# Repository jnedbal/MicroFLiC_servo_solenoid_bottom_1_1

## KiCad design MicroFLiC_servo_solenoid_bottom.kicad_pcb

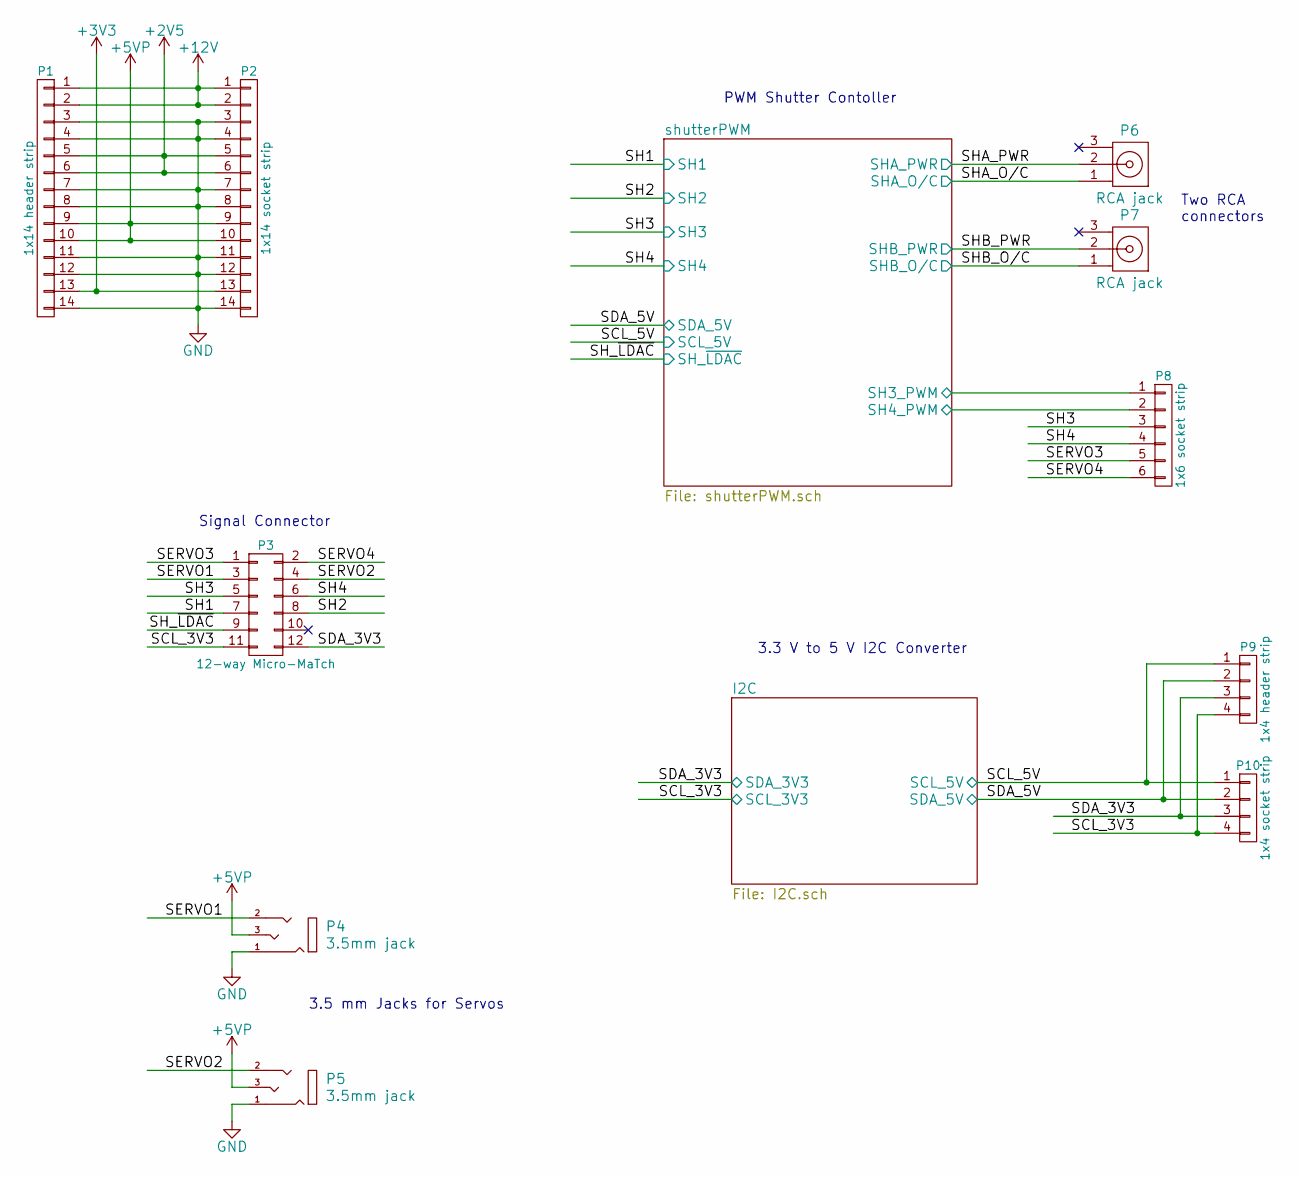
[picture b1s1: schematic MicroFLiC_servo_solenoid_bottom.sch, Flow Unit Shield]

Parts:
P1: 1x14 header strip; Pin_Header_Straight_1x14; Part Number MC34735
P2: 1x14 socket strip; ESQ-114-33-G-S; Part Number ESQ-114-33-G-S
P3: 12-way Micro-MaTch; 1-188275-2; Part Number 8-188275-2
P4, P5: 3.5mm jack; MJ4435-R; Part Number MJ4435-R
P6, P7: RCA jack; PSG01544; Part Number PSG01540
P8: 1x6 socket strip; ESQ-106-33-G-S; Part Number ESQ-106-33-G-S
P9: 1x4 header strip; Pin_Header_Straight_1x04; Part Number M20-9990445
P10: 1x4 socket strip; ESQ-104-33-G-S; Part Number ESQ-104-33-G-S

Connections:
+2V5: P1.5, P1.6, P2.5, P2.6; also elsewhere on the board
+3V3: P1.13, P2.13; also elsewhere on the board
+5VP: P1.9, P1.10, P2.9, P2.10, P4.3, P5.3; also elsewhere on the board
+12V: P1.1, P1.2, P2.1, P2.2; also elsewhere on the board
/I2C/SCL_3V3: P3.11, P9.4, P10.4; also elsewhere on the board
/I2C/SCL_5V: P9.1, P10.1; also elsewhere on the board
/I2C/SDA_3V3: P3.12, P9.3, P10.3; also elsewhere on the board
/I2C/SDA_5V: P9.2, P10.2; also elsewhere on the board
/SERVO1: P3.3, P4.2
/SERVO2: P3.4, P5.2
/SERVO3: P3.1, P8.5
/SERVO4: P3.2, P8.6
/SH3: P3.5, P8.3
/SH4: P3.6, P8.4
/shutterPWM/SH1: P3.7; also elsewhere on the board
/shutterPWM/SH2: P3.8; also elsewhere on the board
/shutterPWM/SH3_PWM: P8.1; also elsewhere on the board
/shutterPWM/SH4_PWM: P8.2; also elsewhere on the board
/shutterPWM/SHA_O/C: P6.1; also elsewhere on the board
/shutterPWM/SHA_PWR: P6.2; also elsewhere on the board
/shutterPWM/SHB_O/C: P7.1; also elsewhere on the board
/shutterPWM/SHB_PWR: P7.2; also elsewhere on the board
/shutterPWM/SH_~LDAC: P3.9; also elsewhere on the board
GND: P1.3, P1.4, P1.7, P1.8, P1.11, P1.12, P1.14, P2.3, P2.4, P2.7, P2.8, P2.11, P2.12, P2.14, P4.1, P5.1; also elsewhere on the board

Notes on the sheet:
Two RCA connectors
3.3 V to 5 V I2C Converter
PWM Shutter Contoller
Signal Connector
3.5 mm Jacks for Servos

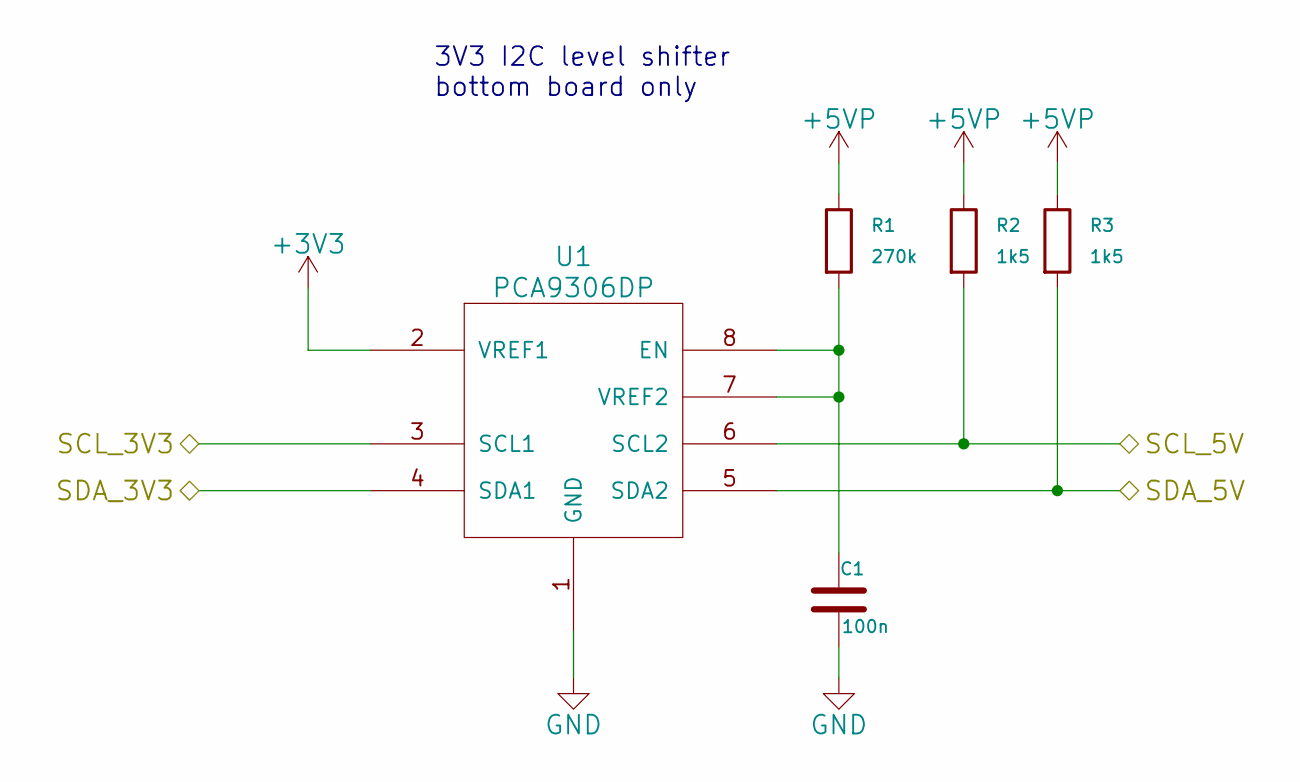
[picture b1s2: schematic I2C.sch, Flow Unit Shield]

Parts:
C1: 100n; C_0805; Part Number MC0805B104K250CT
R1: 270k; R_0805; Part Number MCSR08X2703FTL
R2, R3: 1k5; R_0805; Part Number MCWR08X1501FTL
U1: PCA9306DP; TSSOP-8_3x3mm_Pitch0.65mm; Part Number PCA9306DP

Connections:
+3V3: U1.2 (VREF1); also elsewhere on the board
+5VP: R1.1, R2.1, R3.1; also elsewhere on the board
/I2C/SCL_3V3: U1.3 (SCL1); also elsewhere on the board
/I2C/SCL_5V: R2.2, U1.6 (SCL2); also elsewhere on the board
/I2C/SDA_3V3: U1.4 (SDA1); also elsewhere on the board
/I2C/SDA_5V: R3.2, U1.5 (SDA2); also elsewhere on the board
GND: C1.2, U1.1 (GND); also elsewhere on the board
unnamed: C1.1, R1.2, U1.7 (VREF2), U1.8 (EN)

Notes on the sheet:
3V3 I2C level shifter bottom board only

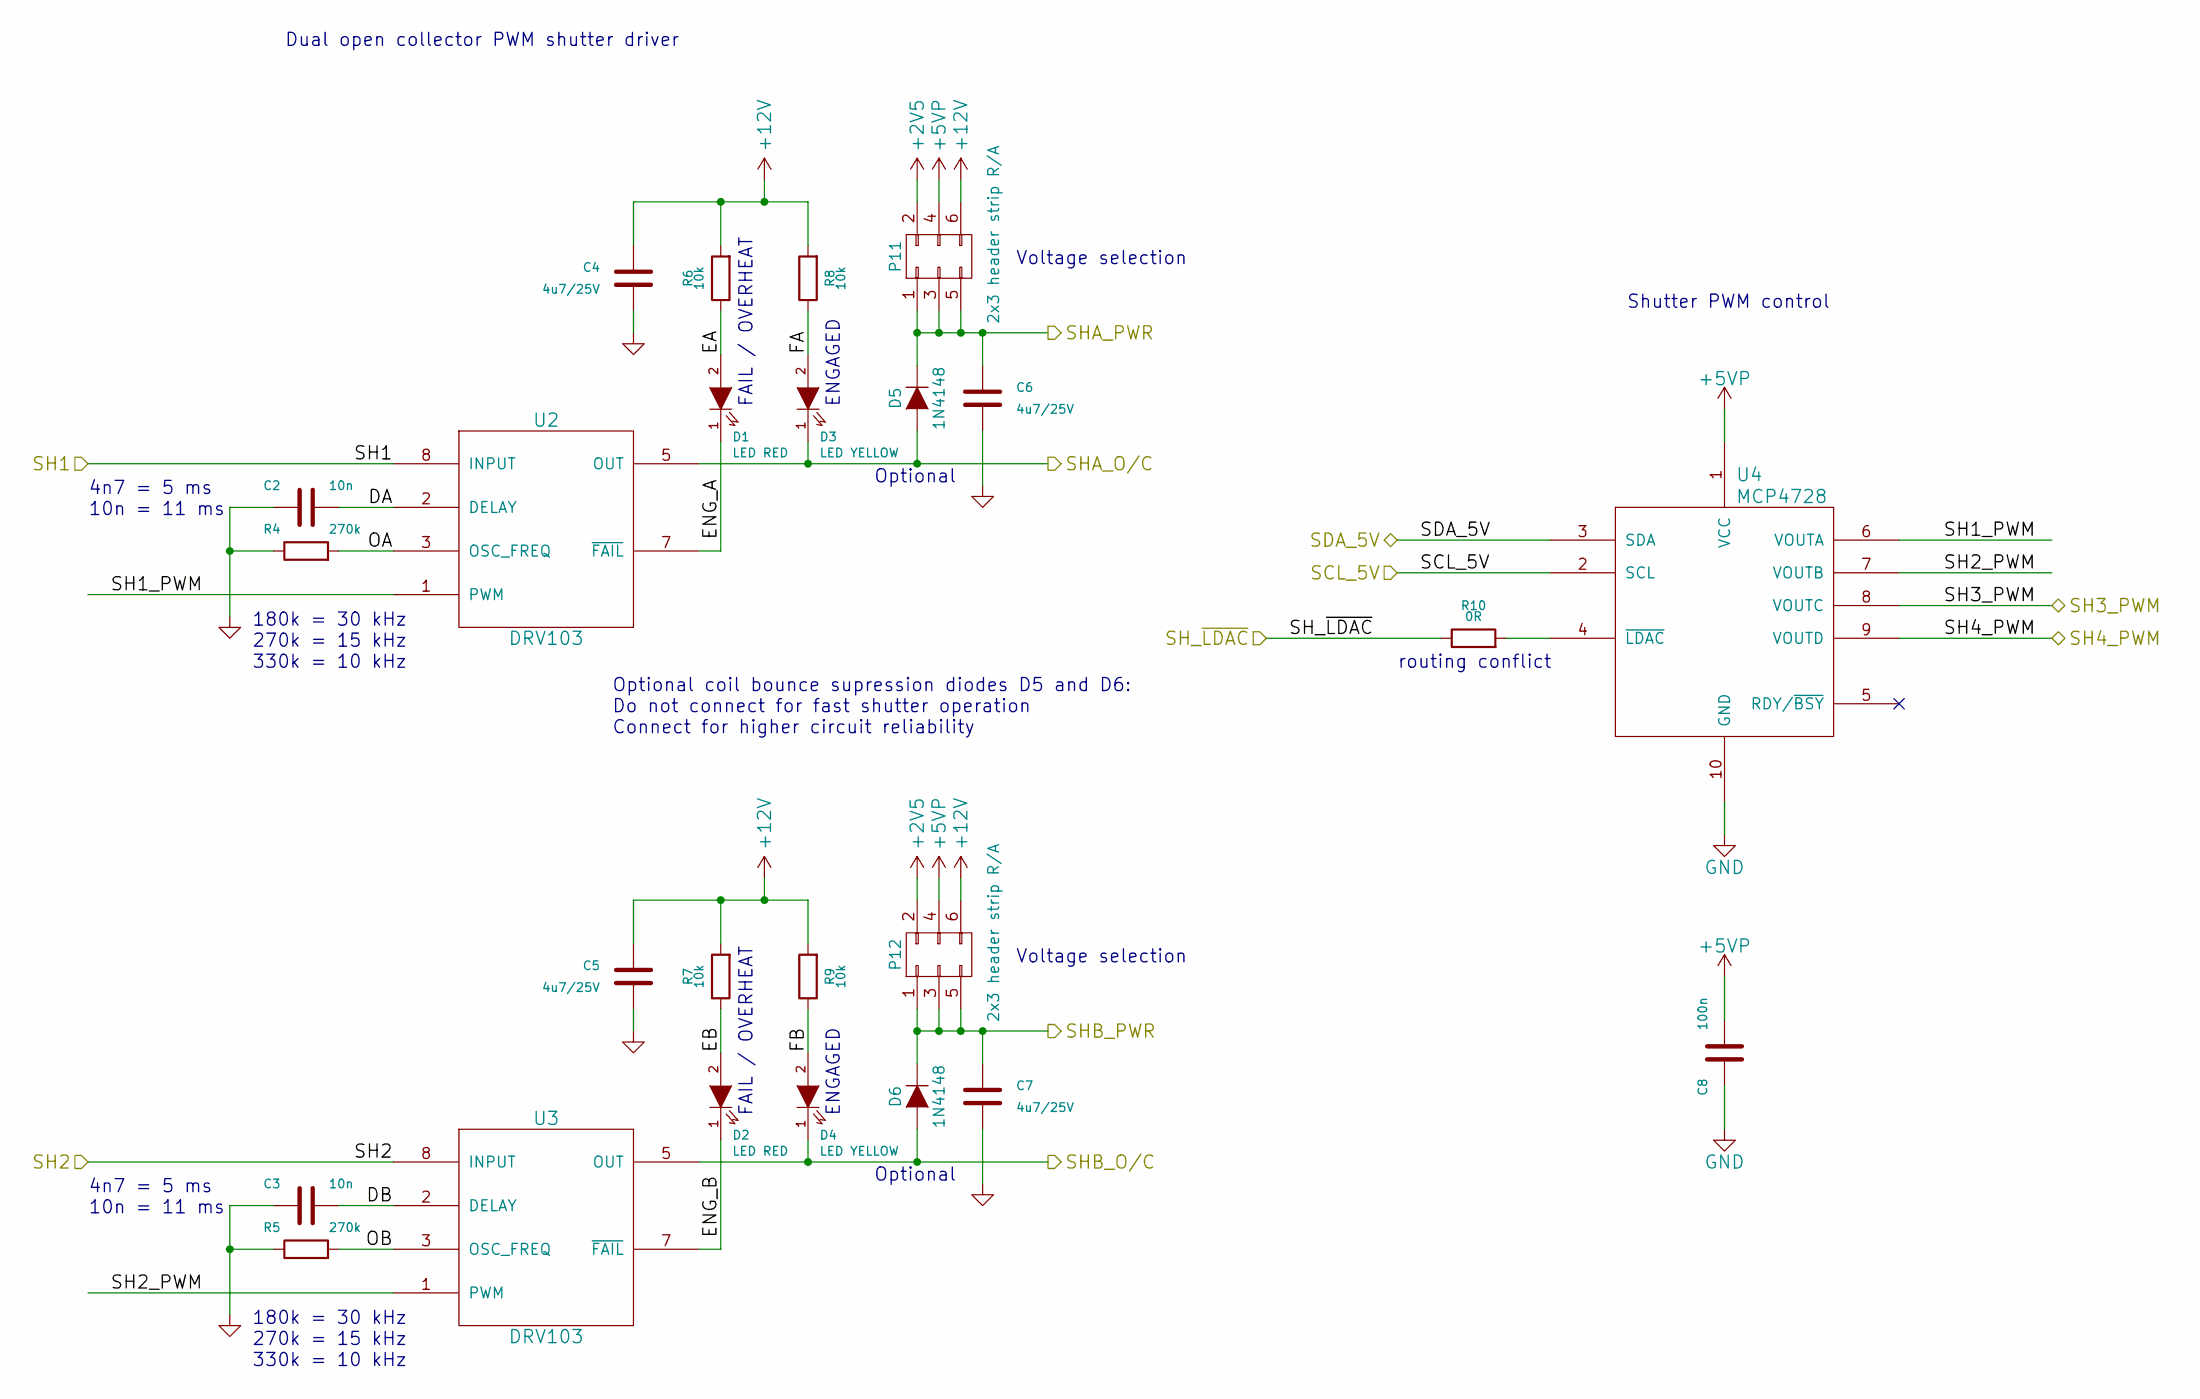
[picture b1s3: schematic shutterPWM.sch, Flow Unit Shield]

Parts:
C2, C3: 10n; C_0805; Part Number MCU0805R103KCT
C4, C5, C6, C7: 4u7/25V; C_0805; Part Number GRM21BR61E475MA12L
C8: 100n; C_0805; Part Number MC0805B104K250CT
D1, D2: LED RED; LED-1206; Part Number HSMS-C150
D3, D4: LED YELLOW; LED-1206; Part Number HSMY-C150
D5, D6: 1N4148; SOD-323; Part Number 1N4148WS
P11, P12: 2x3 header strip R/A; Pin_Header_Angled_2x03; Part Number 2213R-06G
R4, R5: 270k; R_0805; Part Number MCSR08X2703FTL
R6, R7, R8, R9: 10k; R_0805; Part Number MCMR08X1002FTL
R10: 0R; R_0805; Part Number MCMR08X000 PTL
U2, U3: DRV103; SOIC-8_3.9x4.9mm_Pitch1.27mm; Part Number DRV103UG4
U4: MCP4728; MSOP-10_3x3mm_Pitch0.5mm; Part Number MCP4728-E/UN

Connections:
+2V5: P11.2, P12.2; also elsewhere on the board
+5VP: C8.2, P11.4, P12.4, U4.1 (VCC); also elsewhere on the board
+12V: C4.2, C5.2, P11.6, P12.6, R6.2, R7.2, R8.2, R9.2, U2.6 (+12V), U3.6 (+12V); also elsewhere on the board
/I2C/SCL_5V: U4.2 (SCL); also elsewhere on the board
/I2C/SDA_5V: U4.3 (SDA); also elsewhere on the board
/shutterPWM/DA: C2.2, U2.2 (DELAY)
/shutterPWM/DB: C3.2, U3.2 (DELAY)
/shutterPWM/EA: D1.2 (A), R6.1
/shutterPWM/EB: D2.2 (A), R7.1
/shutterPWM/ENG_A: D1.1 (K), U2.7 (~FAIL)
/shutterPWM/ENG_B: D2.1 (K), U3.7 (~FAIL)
/shutterPWM/FA: D3.2 (A), R8.1
/shutterPWM/FB: D4.2 (A), R9.1
/shutterPWM/OA: R4.2, U2.3 (OSC_FREQ)
/shutterPWM/OB: R5.2, U3.3 (OSC_FREQ)
/shutterPWM/SH1: U2.8 (INPUT); also elsewhere on the board
/shutterPWM/SH1_PWM: U2.1 (PWM), U4.6 (VOUTA)
/shutterPWM/SH2: U3.8 (INPUT); also elsewhere on the board
/shutterPWM/SH2_PWM: U3.1 (PWM), U4.7 (VOUTB)
/shutterPWM/SH3_PWM: U4.8 (VOUTC); also elsewhere on the board
/shutterPWM/SH4_PWM: U4.9 (VOUTD); also elsewhere on the board
/shutterPWM/SHA_O/C: D3.1 (K), D5.2 (A), U2.5 (OUT); also elsewhere on the board
/shutterPWM/SHA_PWR: C6.2, D5.1 (K), P11.1, P11.3, P11.5; also elsewhere on the board
/shutterPWM/SHB_O/C: D4.1 (K), D6.2 (A), U3.5 (OUT); also elsewhere on the board
/shutterPWM/SHB_PWR: C7.2, D6.1 (K), P12.1, P12.3, P12.5; also elsewhere on the board
/shutterPWM/SH_~LDAC: R10.1; also elsewhere on the board
GND: C2.1, C3.1, C4.1, C5.1, C6.1, C7.1, C8.1, R4.1, R5.1, U2.4 (GND), U3.4 (GND), U4.10 (GND); also elsewhere on the board
unnamed: R10.2, U4.4 (~LDAC)

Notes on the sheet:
Dual open collector PWM shutter driver
Optional coil bounce supression diodes D5 and D6: Do not connect for fast shutter operation Connect for higher circuit reliability
180k = 30 kHz 270k = 15 kHz 330k = 10 kHz
4n7 = 5 ms 10n = 11 ms
Shutter PWM control
FAIL / OVERHEAT
ENGAGED
routing conflict
Optional
Voltage selection

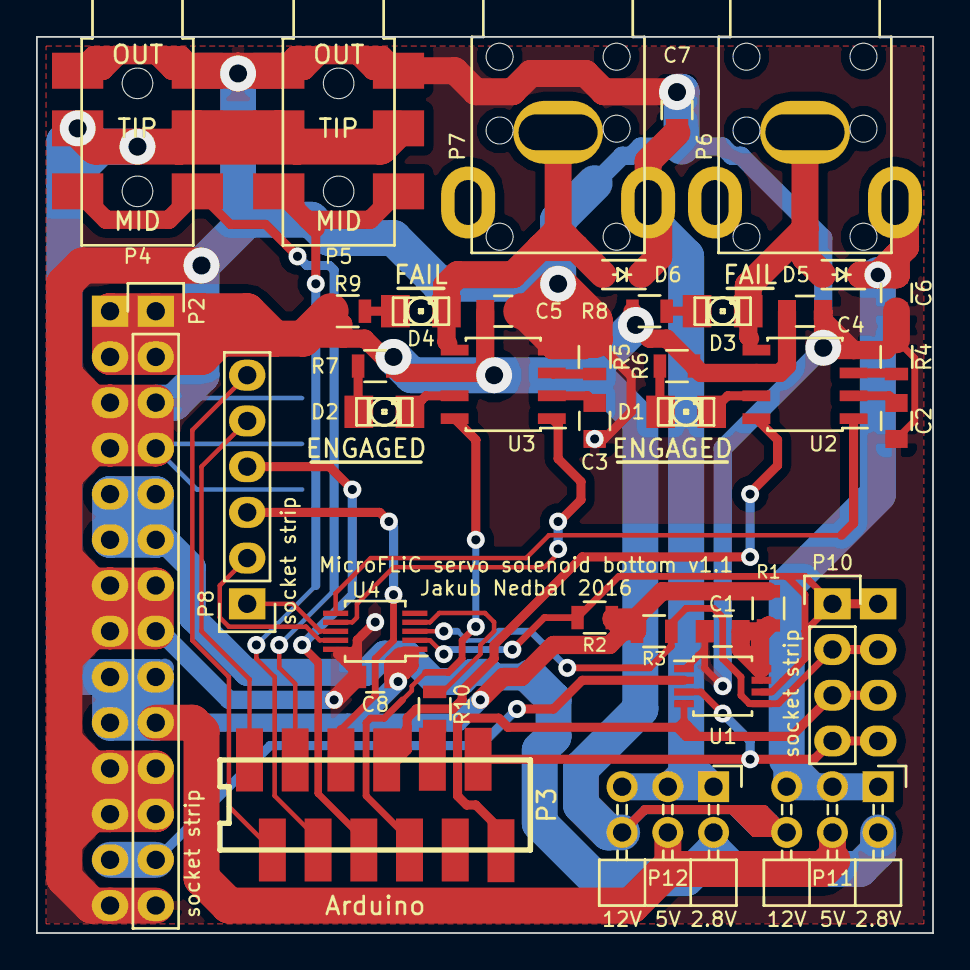
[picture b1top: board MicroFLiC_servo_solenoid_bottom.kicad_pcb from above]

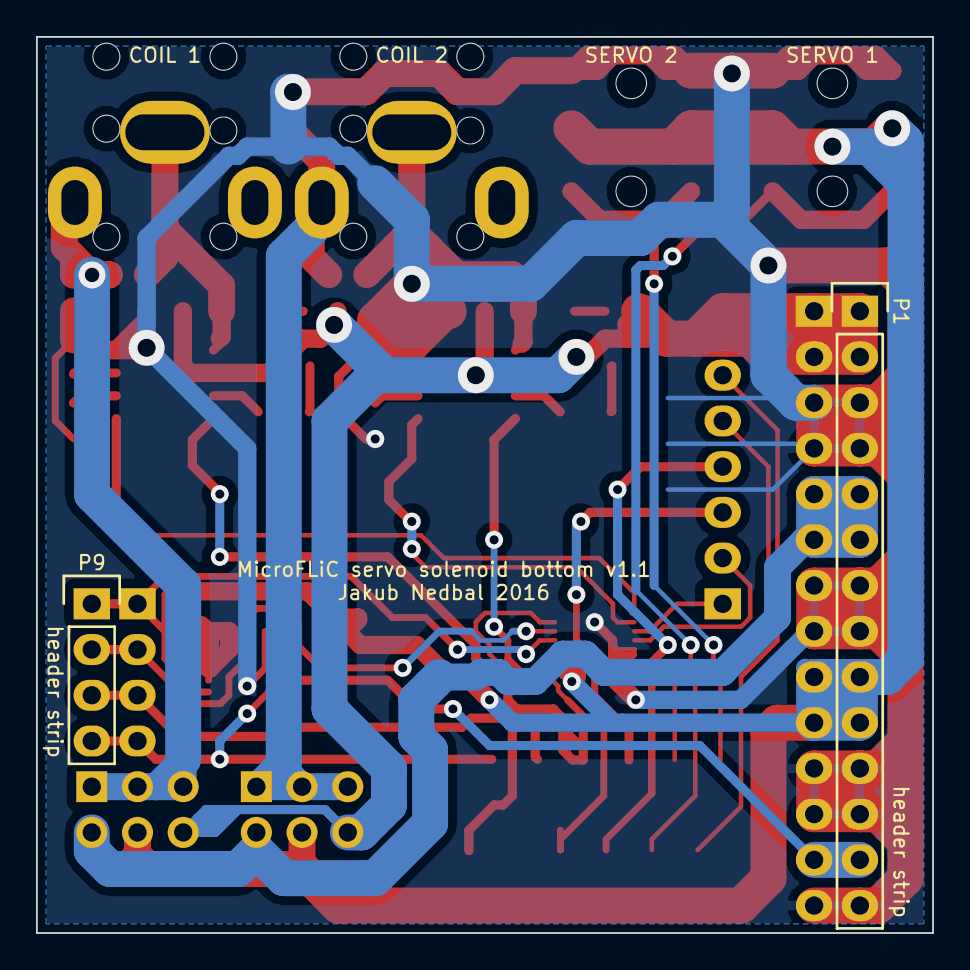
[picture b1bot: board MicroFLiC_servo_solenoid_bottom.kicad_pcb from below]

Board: 2 copper layers, 49.8 x 49.8 mm, 40 parts (2 on the bottom side), 38 nets.

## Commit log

2016-02-29 Added board name, created new Gerber plots
2016-03-02 Fixed jack part values
2016-03-02 Added better de-bouncing diode description
2016-03-18 Added pullup resistors to I2C
2016-03-18 Changed ENGAGED LED anode to +5V, changed SOD-323 packages.
2016-03-18 Changed 100n->100p capacitor on the I2C level shifter
